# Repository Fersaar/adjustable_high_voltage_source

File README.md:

# adjustable_high_voltage_source
This project was developed as part of the [contactless electrostatic grippers](https://github.com/Fersaar/contactless_electrostatic_gripper) project. To control the individual gripper zones, it is essential to supply them with a variable voltage ranging from 0V to 1000V. The required current is minimal, as only the individual gripper electrodes need to be charged. In the final gripper design, this circuit will be positioned between the microcontroller and the gripper.

## Requirements

- Variable output voltage between 0V and 1000V
- External supply of 1000V DC
- Linear voltage regulation
- Input: PWM signal with 3.3V and variable duty cycle
- Cut-off frequency of 1kHz
- As cost-effective and straightforward as possible

## Design

The core of the design is a half-bridge circuit utilizing the "FAN73912mx" driver, which can withstand voltages up to 1200V. However, it is not isolated, so all ground potentials must be interconnected. The circuit design follows the reference layout provided by the driver, incorporating a bootstrap circuit to switch the MOSFETs. The output is filtered through an RC gate to eliminate the PWM signal and provide a stable DC voltage. The switching frequency is set at 20kHz. While the design may not be optimal, it effectively meets the application’s requirements.

## PCB

The completed circuit board is designed to allow multiple units to be stacked vertically, with supply lines that can be easily looped through.

| | |
|--|---|
| | |
| single half bridge|stacked half bridges |

The quiescent current at 1000V and 20kHz is approximately 3 mA. The minimum voltage resolution is determined by the PWM resolution; for instance, with a 12-bit signal, the resolution is about 0.244V.

The voltage can be controlled linearly as desired: 

### BOM

| Part | Quantity | Link |  |
|--------------------------------------------------------------------------|----------|-----------------------------------------------------------------------------------------------------------|---------------|
| fan73912mx | 1 | https://de.farnell.com/on-semiconductor/fan73912mx/gate-treiber-halbbr-cke-wsoic/dp/2748785?st=fan73912mx | IC1 |
| electrolytic capacitor, 4.7 µF, 50 V | 1 | https://de.farnell.com/rubycon/50yxf4r7mefc5x11/kondensator-4-7-f-50v-20/dp/2811491 | C2 |
| ceramic multilayer capacitor, 0.47 µF, 50 V | 1 | https://de.farnell.com/murata/rder71h474k1m1h03a/kondensator-0-47uf-50v-mlcc-radial/dp/2990810 | C1 C_Boot |
| 47 Ohm, +-5%, 350V | 2 | https://de.farnell.com/multicomp/mcf-0-5w-47r/kohlesch-widerstand-47r-5-500mw/dp/9338802 | R1&R2 |
| Resistor 1210 [Metric 3225], 2.2 ohm, KTR Series, 600 V | 3 | https://de.farnell.com/rohm/ktr25jzpf2r20/dickschichtwiderstand-2r2-1-1210/dp/2802500 | R3-R7 |
| diode 1.2 kV, 1 A, single, 1.65 V, 75 ns, 18 A | 1 | https://de.farnell.com/stmicroelectronics/stth112u/diode-ku-erholzeit-1a-1200v-smd/dp/1467508 | D1 |
| MOSFET, n-channel, 1.5 kV, 1.3 A, 6 ohm | 2 | https://de.farnell.com/stmicroelectronics/stw3n150/mosfet-n-kanal-1500v-2-5a-to-247/dp/1752211?st=mosfet | Q1, Q2 |
| screw terminal 2 poles | 4 | https://de.farnell.com/lumberg/krm-02/klemme-leiterpl-polyamid-2pol/dp/1177875 | J2,J4, J6, J7 |
| screw terminal 3 pole | 4 | https://de.farnell.com/camdenboss/ctbp5000-3/klemmenblock-wire-to-board-3pos/dp/2527548 | J1,J2,J4 |
| Ceramic Disc Capacitor, 100 pF, 3 kV, F Series, ± 10%, S3N, 7.5 mm | 1 | https://de.farnell.com/vishay/f101k25s3nr63k7r/kondensator-100pf-3-kv-10-s3n/dp/2860045 | C3 |
| 3MOhm, 2kV, +-5% | 1 | https://de.farnell.com/multicomp/mchvr0ajtfu3004/dicksch-widerstand-3m-5-0-5w-2010/dp/2826728 | R10 |
| 3MOhm, 2kV, +-5% | 1 | https://de.farnell.com/multicomp/mchvr0ajtfu3004/dicksch-widerstand-3m-5-0-5w-2010/dp/2826728 | |

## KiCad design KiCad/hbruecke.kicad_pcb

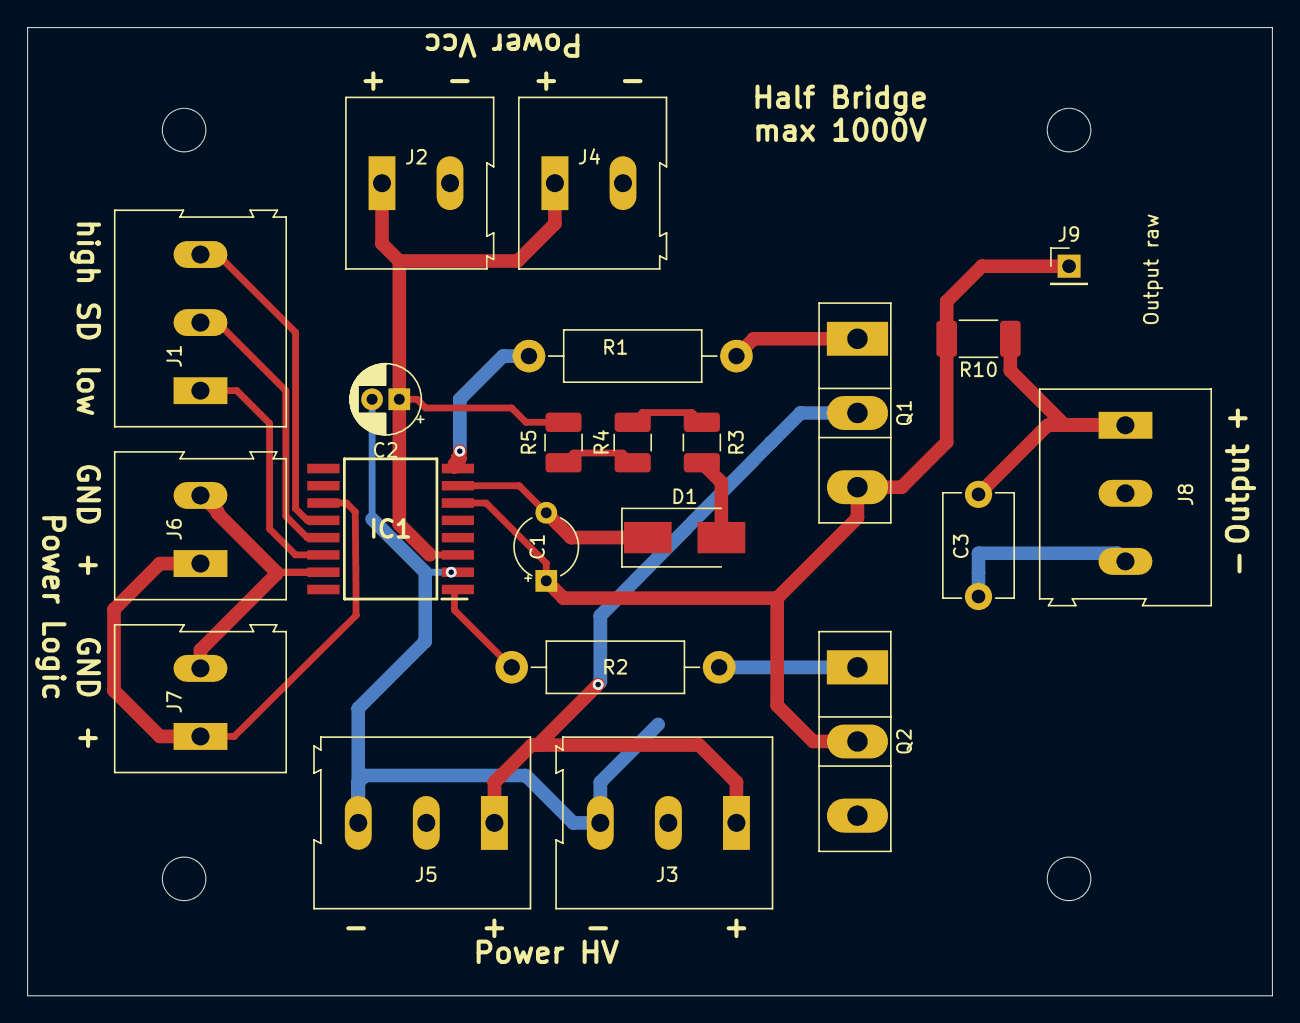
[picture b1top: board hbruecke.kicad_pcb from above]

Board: 2 copper layers, 91.4 x 71.1 mm, 26 parts (0 on the bottom side), 18 nets.

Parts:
C1: 0.33u; CP_Radial_Tantal_D4.5mm_P5.00mm
C2: 3u3; CP_Radial_D5.0mm_P2.00mm
C3: 150p; C_Disc_D7.5mm_W5.0mm_P7.50mm
D1: 1200V; D_SMB_Handsoldering
H1, H2, H3, H4: MountingHole; MountingHole_3.2mm_M3
IC1: FAN73912MX; SOIC127P1032X265-16N
J1: Input_Signal; TerminalBlock_Altech_AK300-3_P5.00mm
J2: Input_VCC; TerminalBlock_Altech_AK300-2_P5.00mm
J3: Input_HV; TerminalBlock_Altech_AK300-3_P5.00mm
J4: Output_VCC; TerminalBlock_Altech_AK300-2_P5.00mm
J5: Output_HV; TerminalBlock_Altech_AK300-3_P5.00mm
J6: Input_Logic; TerminalBlock_Altech_AK300-2_P5.00mm
J7: Output_Logic; TerminalBlock_Altech_AK300-2_P5.00mm
J8: Output_Elektrode; TerminalBlock_Altech_AK300-3_P5.00mm
J9: Output_Raw; PinHeader_1x01_P2.54mm_Vertical
Q1, Q2: _; TO-247-3_Vertical
R1, R2: 47; R_Axial_DIN0411_L9.9mm_D3.6mm_P15.24mm_Horizontal
R3, R4, R5: 2.2; R_1210_3225Metric_Pad1.42x2.65mm_HandSolder
R10: 240k; R_2010_5025Metric_Pad1.52x2.65mm_HandSolder

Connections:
+1200: J3.1, J5.1, Q1.2
COM: C2.2, C3.2, IC1.2, J2.2, J3.3, J4.2, J5.3, J8.3, Q2.3
GND: IC1.15, J6.2, J7.2
unnamed: C3.1, J8.1, R10.1
unnamed: D1.2, R3.2
unnamed: IC1.1, R2.2
unnamed: IC1.8, R1.2
unnamed: Q1.1, R1.1
unnamed: Q2.1, R2.1
unnamed: R3.1, R4.2
unnamed: R4.1, R5.2
VB: C1.2, D1.1, IC1.7
VCC: C2.1, IC1.3, J2.1, J4.1, R5.1
VS: C1.1, IC1.6, J9.1, Q1.3, Q2.2, R10.2
V_DD,logicsupply: IC1.11, J6.1, J7.1
uC_High: IC1.12, J1.3
uC_Low: IC1.14, J1.1
uC_SD: IC1.13, J1.2

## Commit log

2021-04-02 inital commit
